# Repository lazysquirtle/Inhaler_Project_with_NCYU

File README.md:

# Inhaler_Project_with_NYCU
System Design

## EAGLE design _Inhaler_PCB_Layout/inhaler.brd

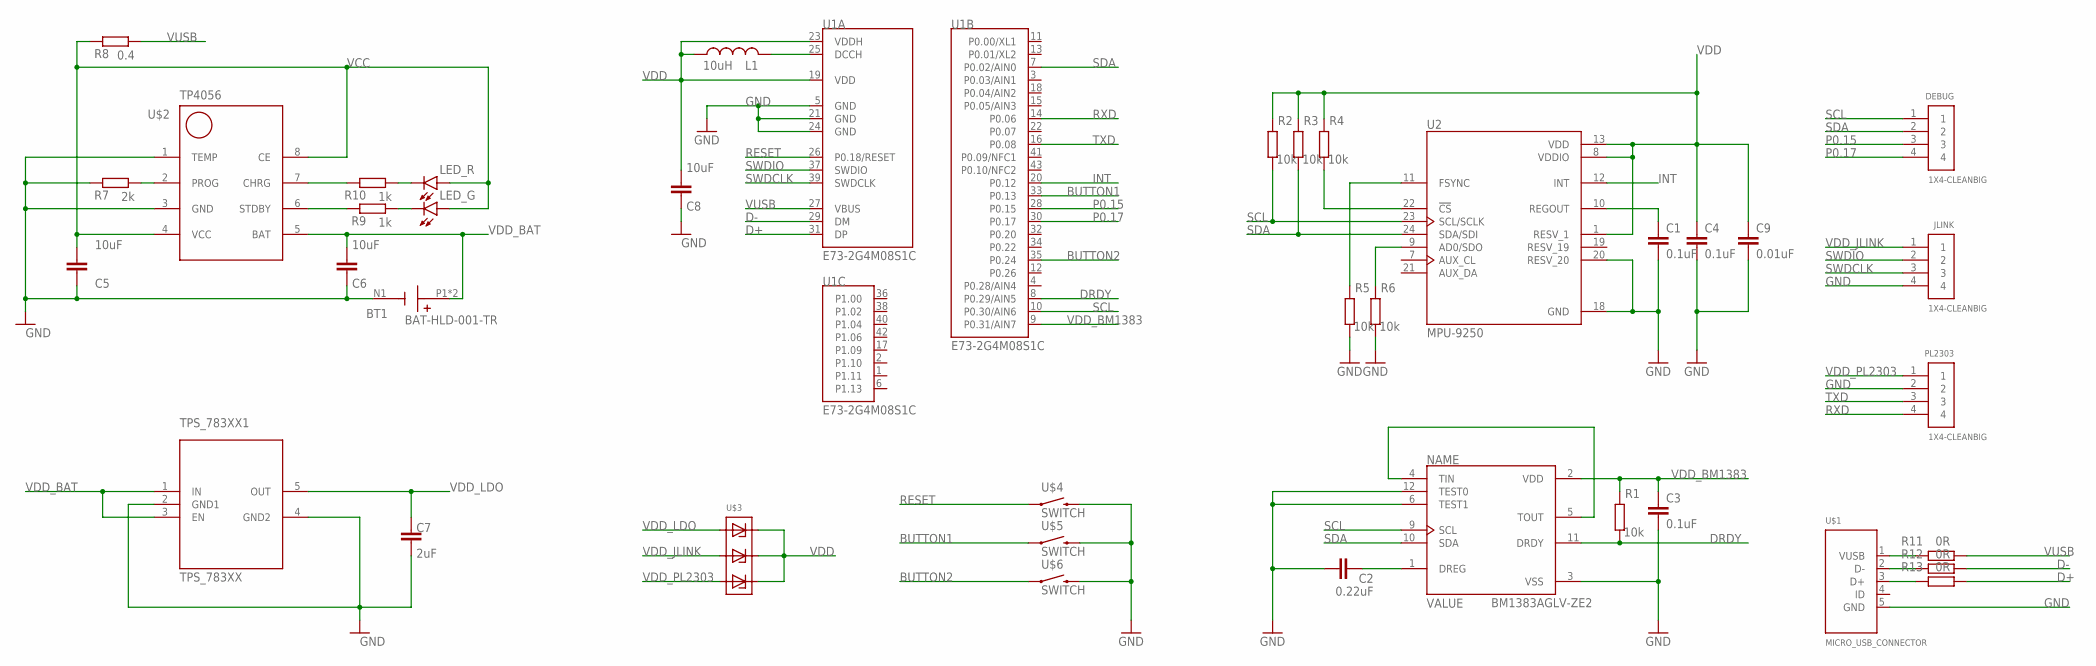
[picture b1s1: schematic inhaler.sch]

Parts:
BT1: BAT-HLD-001-TR; BAT_BAT-HLD-001-TR
C1, C3, C4: 0.1uF; C0805
C2: 0.22uF; C0805
C5, C6, C8: 10uF; C0805
C7: 2uF; C0805
C9: 0.01uF; C0805
DEBUG: 1X4-CLEANBIG; 1X04-CLEANBIG
JLINK: 1X4-CLEANBIG; 1X04-CLEANBIG
L1: 10uH; L0805
LED_G: LEDSMT1206; 1206
LED_R: LEDSMT1206; 1206
PL2303: 1X4-CLEANBIG; 1X04-CLEANBIG
R1, R2, R3, R4, R5, R6: 10k; R0805
R7: 2k; R0805
R8: 0.4; R0805
R9, R10: 1k; R0805
R11, R12, R13: 0R; R0805
TPS_783XX1: TPS_783XX; SOT65P280X145-5N
U1: E73-2G4M08S1C
U2: MPU-9250; QFN40P300X300X105-24N
U3: BM1383AGLV-ZE2; PQFN55P250X250X100-12N
U$1: MICRO_USB_CONNECTOR; MICRO_USB_4LEGS
U$2: TP4056; SOP8
U$3: SD103ATW; SOT363
U$4, U$5, U$6: SWITCH; SWITCH_2PIN

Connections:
BUTTON1: U1.33 (P0.13), U$5.1
BUTTON2: U1.35 (P0.24), U$6.1
D+: R13.1, U1.31 (DP)
D-: R12.1, U1.29 (DM)
DRDY: R1.1, U1.8 (P0.29/AIN5), U3.11 (DRDY)
GND: BT1.N1 (-), C1.2, C2.1, C3.2, C4.2, C5.1, C6.1, C7.1, C8.1, C9.2, JLINK.4, PL2303.2, R5.1, R6.1, R7.2, TPS_783XX1.2 (GND1), TPS_783XX1.4 (GND2), U1.5 (GND), U1.21 (GND), U1.24 (GND), U2.18 (GND), U2.20 (RESV_20), U3.3 (VSS), U3.6 (TEST1), U3.12 (TEST0), U$1.5 (GND), U$2.1 (TEMP), U$2.3 (GND), U$4.2, U$5.2, U$6.2
INT: U1.20 (P0.12), U2.12 (INT)
unnamed: C1.1, U2.10 (REGOUT)
unnamed: U3.4 (TIN), U3.5 (TOUT)
unnamed: C2.2, U3.1 (DREG)
unnamed: R4.1, U2.22 (!CS)
unnamed: R5.2, U2.11 (FSYNC)
unnamed: R7.1, U$2.2 (PROG)
unnamed: R6.2, U2.9 (AD0/SDO)
unnamed: R10.2, U$2.7 (CHRG)
unnamed: L1.2, U1.25 (DCCH)
unnamed: R9.2, U$2.6 (STDBY)
unnamed: LED_R.C, R10.1
unnamed: LED_G.C, R9.1
unnamed: R13.2, U$1.3 (D+)
unnamed: R11.2, U$1.1 (VUSB)
unnamed: R12.2, U$1.2 (D-)
P0.15: DEBUG.3, U1.28 (P0.15)
P0.17: DEBUG.4, U1.30 (P0.17)
RESET: U1.26 (P0.18/RESET), U$4.1
RXD: PL2303.4, U1.14 (P0.06)
SCL: DEBUG.1, R2.1, U1.10 (P0.30/AIN6), U2.23 (SCL/SCLK), U3.9 (SCL)
SDA: DEBUG.2, R3.1, U1.7 (P0.02/AIN0), U2.24 (SDA/SDI), U3.10 (SDA)
SWDCLK: JLINK.3, U1.39 (SWDCLK)
SWDIO: JLINK.2, U1.37 (SWDIO)
TXD: PL2303.3, U1.16 (P0.08)
VCC: C5.2, LED_G.A, LED_R.A, R8.2, U$2.4 (VCC), U$2.8 (CE)
VDD: C4.1, C8.2, C9.1, L1.1, R2.2, R3.2, R4.2, U1.19 (VDD), U1.23 (VDDH), U2.1 (RESV_1), U2.8 (VDDIO), U2.13 (VDD), U$3.2, U$3.4, U$3.6
VDD_BAT: BT1.P1 (+), BT1.P2 (+), C6.2, TPS_783XX1.1 (IN), TPS_783XX1.3 (EN), U$2.5 (BAT)
VDD_BM1383: C3.1, R1.2, U1.9 (P0.31/AIN7), U3.2 (VDD)
VDD_JLINK: JLINK.1, U$3.3
VDD_LDO: C7.2, TPS_783XX1.5 (OUT), U$3.1
VDD_PL2303: PL2303.1, U$3.5
VUSB: R8.1, R11.1, U1.27 (VBUS)

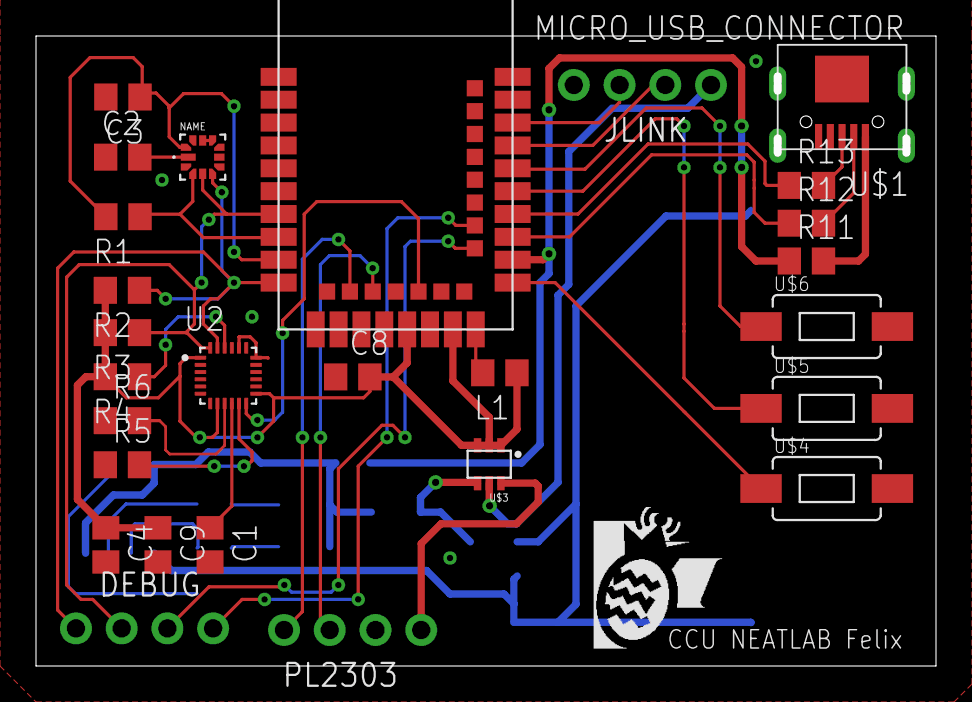
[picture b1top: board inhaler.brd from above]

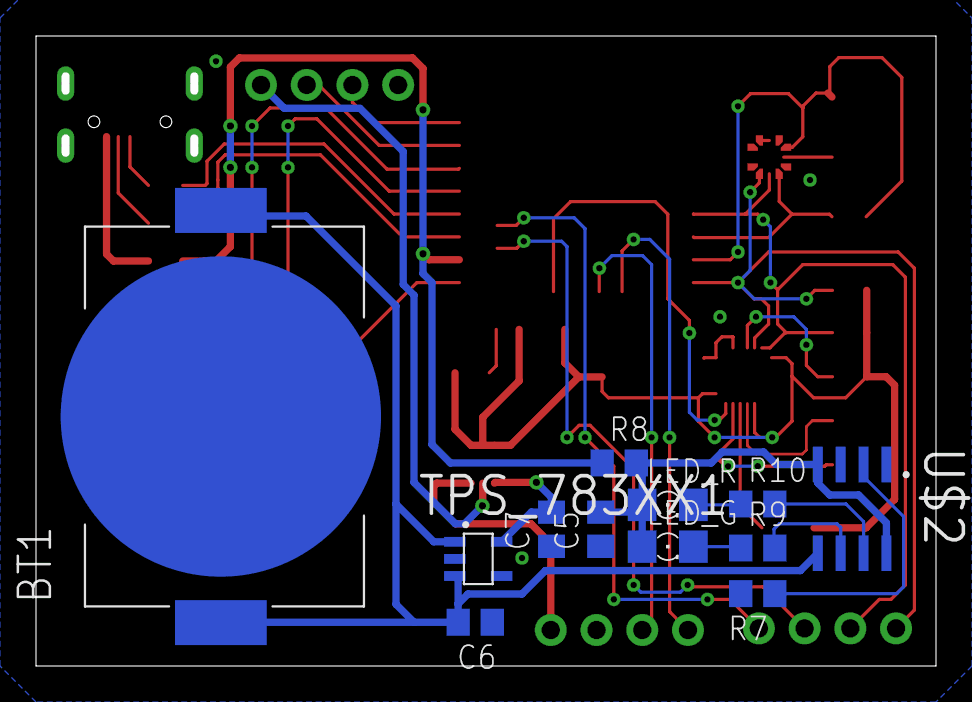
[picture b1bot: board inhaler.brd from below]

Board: 2 copper layers, 49.5 x 34.5 mm, 40 parts (12 on the bottom side), 39 nets.

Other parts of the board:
U$7: LOGO_SCALE_1.9

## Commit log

2023-01-31 PCB Layout
    add PCB Layout
2023-01-31 add PCB Layout
